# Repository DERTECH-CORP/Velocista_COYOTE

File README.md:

# Velocista "Coyote" - Robot Seguidor de Línea

## Descripción

El velocista "Coyote" es un robot seguidor de línea de alto rendimiento diseñado para competir en desafíos de velocidad y precisión. Este repositorio contiene el firmware, el diseño de hardware electrónico y los modelos 3D relacionados con el robot Coyote. Aquí encontrarás toda la información necesaria para comprender el robot seguidor de línea Coyote.

## Características principales

- **Seguimiento de línea preciso**: Coyote utiliza los sensores ópticos QRE1113 para seguir líneas con precisión y rapidez. Su firmware incorpora algoritmos de control PID que garantizan un seguimiento suave y estable.

- **Velocidad y agilidad**: Utiliza sus motores de RPM2000 con diseño aerodinámico, El Coyote puede alcanzar altas velocidades y realizar maniobras bruscas gracias a sus ruedas anchas que le ayudan a tener mejor agarre en la pista.

- **Firmware personalizable**: El firmware del robot está escrito en lenguaje C++ y se basa en la plataforma de desarrollo ESP32. Este micricontrolador nos ayuda mucho ya que tiene antena wifi/bluetooth integrada y gracias a eso podemos debuguear y calibrar el robot sin necesidad de conectarlo a la computadora.

## Contenido del repositorio

- **/firmware**: En esta carpeta encontrarás el código fuente del firmware utilizado en Coyote. El firmware está escrito en lenguaje C++ y se basa en la plataforma de desarrollo ESP32. Incluye los algoritmos de control, la lógica de seguimiento de línea y la comunicación con los sensores y actuadores del robot ademas de la interfaz bluetooth.

- **/hardware**: Aquí se encuentran los diseños y esquemas del hardware electrónico utilizado en Coyote. Estos archivos incluyen los esquemas de conexión y los diagramas de circuitos.

- **/3D**: En esta carpeta encontrarás los modelos 3D del robot Coyote. Se pueden utilizar para visualizar, modificar y fabricar las partes físicas del robot.

¡Gracias por tu interés en Coyote!

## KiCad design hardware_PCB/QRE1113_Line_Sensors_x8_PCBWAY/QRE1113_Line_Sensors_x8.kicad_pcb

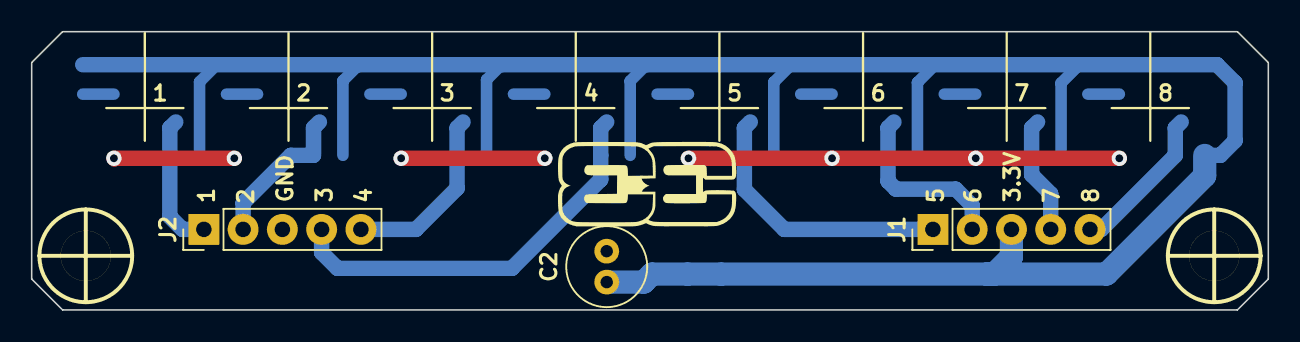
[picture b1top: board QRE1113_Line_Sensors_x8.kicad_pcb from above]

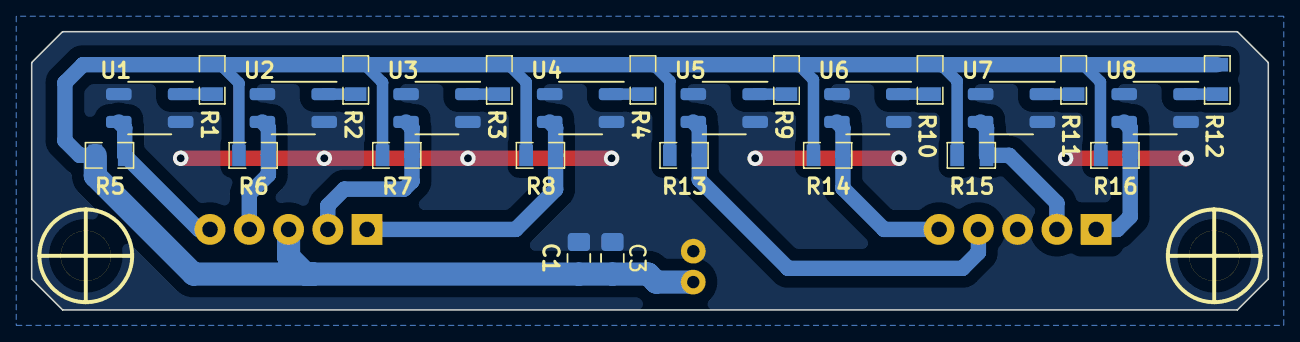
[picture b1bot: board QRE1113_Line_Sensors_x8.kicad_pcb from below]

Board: 2 copper layers, 80.0 x 18.0 mm, 31 parts (26 on the bottom side), 18 nets.

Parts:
C1, C3: 100nf; C_0805_2012Metric_Pad1.18x1.45mm_HandSolder
C2: 100uf; C_Radial_D5.0mm_H11.0mm_P2.00mm
H1, H2: HOLE; Separador_M3_5mm
J1, J2: Conn_01x05_Pin; PinHeader_1x05_P2.54mm_Vertical
R1, R2, R3, R4, R9, R10, R11, R12: 100; R_0805
R5, R6, R7, R8, R13, R14, R15, R16: 10k; R_0805
U1, U2, U3, U4, U5, U6, U7, U8: QRE1113GR; OnSemi_CASE100CY

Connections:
+3V3: C1.1, C2.1, C3.1, J1.3, R1.1, R2.1, R3.1, R4.1, R5.2, R6.2, R7.2, R8.2, R9.1, R10.1, R11.1, R12.1, R13.2, R14.2, R15.2, R16.2
/OUT_1: J1.5, R5.1, U1.3
/OUT_2: J1.4, R6.1, U2.3
/OUT_3: J1.2, R7.1, U3.3
/OUT_4: J1.1, R8.1, U4.3
/OUT_5: J2.4, R13.1, U5.3
/OUT_6: J2.5, R14.1, U6.3
/OUT_7: J2.2, R15.1, U7.3
/OUT_8: J2.1, R16.1, U8.3
GND: C1.2, C2.2, C3.2, J2.3, U1.2 (K), U1.4, U2.2 (K), U2.4, U3.2 (K), U3.4, U4.2 (K), U4.4, U5.2 (K), U5.4, U6.2 (K), U6.4, U7.2 (K), U7.4, U8.2 (K), U8.4
unnamed: R1.2, U1.1 (A)
unnamed: R2.2, U2.1 (A)
unnamed: R3.2, U3.1 (A)
unnamed: R4.2, U4.1 (A)
unnamed: R9.2, U5.1 (A)
unnamed: R10.2, U6.1 (A)
unnamed: R11.2, U7.1 (A)
unnamed: R12.2, U8.1 (A)

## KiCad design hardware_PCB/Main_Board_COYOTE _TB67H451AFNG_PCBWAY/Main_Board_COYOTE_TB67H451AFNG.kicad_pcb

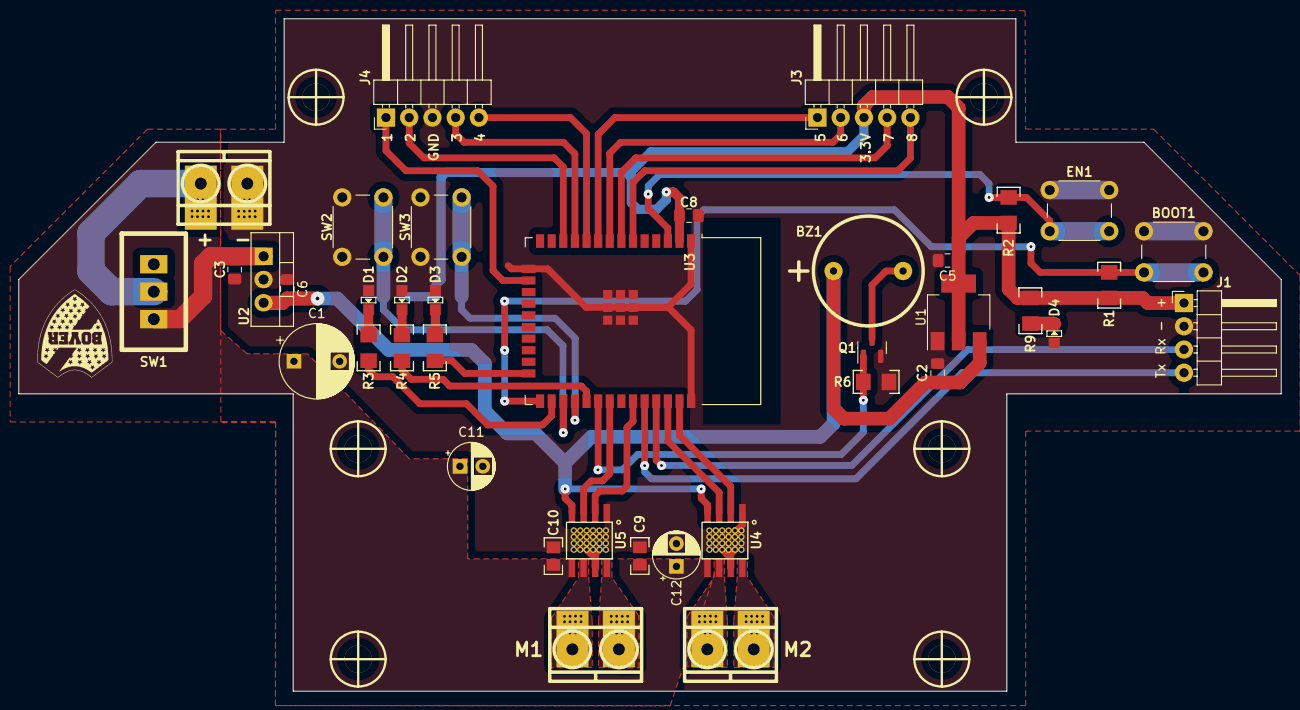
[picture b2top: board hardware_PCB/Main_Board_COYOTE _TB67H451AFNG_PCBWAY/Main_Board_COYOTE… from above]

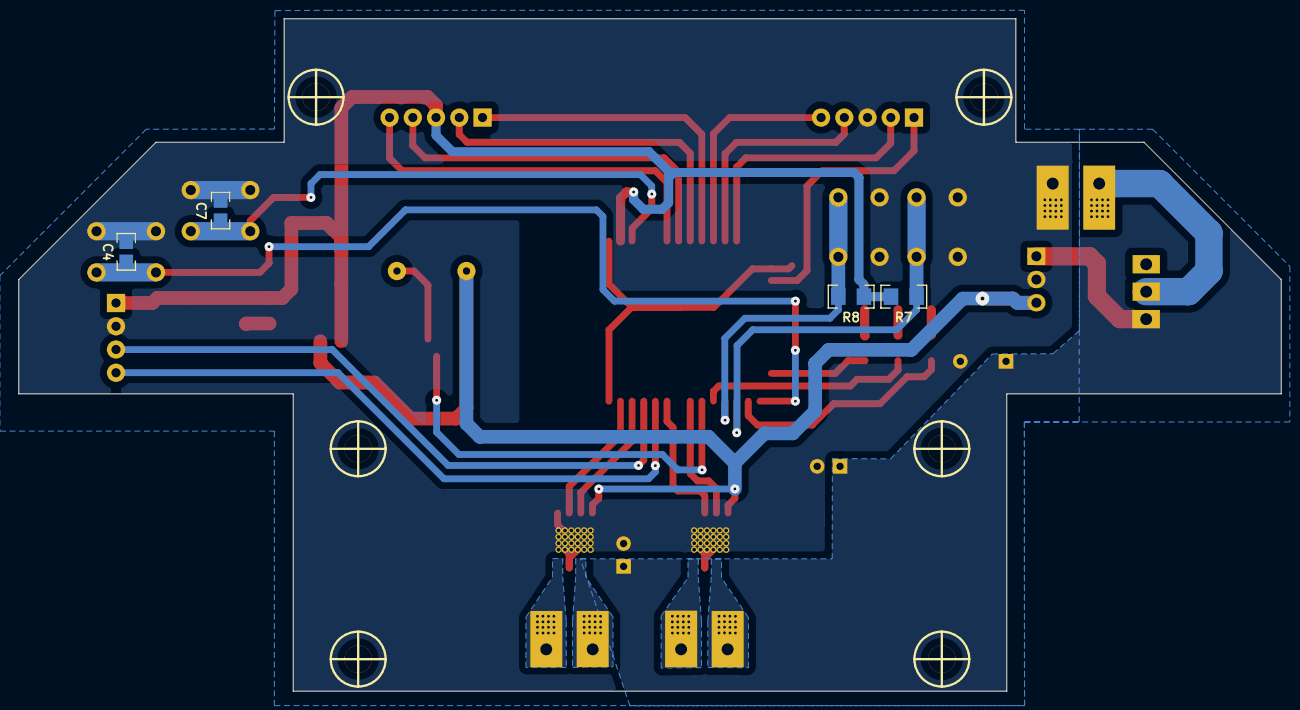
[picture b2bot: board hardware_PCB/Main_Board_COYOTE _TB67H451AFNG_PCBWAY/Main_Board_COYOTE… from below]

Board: 2 copper layers, 138.0 x 73.5 mm, 49 parts (4 on the bottom side), 36 nets.

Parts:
BOOT1: SW_Push; SW_PUSH_6mm_H5mm
BZ1: Buzzer; Buzzer_12mm
C1: 100uF 35V; CP_Radial_D8.0mm_P5.00mm
C2, C3, C5, C6, C8: 1uF; C_0805_2012Metric_Pad1.18x1.45mm_HandSolder
C4, C7: 1n; C_0805
C9, C10: 100nF; C_0805
C11, C12: 100uF 35V; CP_Radial_D5.0mm_P2.50mm
D1, D2, D3, D4: LED; Led_0805
EN1: SW_Push; SW_PUSH_6mm_H5mm
H1, H2, H3, H4, H5, H6: Mounting_Hole; hole_3mm
J1: FTDI; PinHeader_1x04_P2.54mm_Horizontal
J2: + -; BORNERA2_AZUL_VIAS
J3, J4: Conn_01x05_Pin; PinHeader_1x05_P2.54mm_Horizontal
J5: M2; BORNERA2_AZUL_VIAS
J6: M1; BORNERA2_AZUL_VIAS
Q1: 2N7002; SOT-23
R1: 1OK; R_1206
R2, R6: 10K; R_1206
R3, R4, R5, R9: 220; R_1206
R7, R8: 4K7; R_1206
SW1: SW_SPST; SW_SPDT_TH_Vertical
SW2: STRATEGY; SW_PUSH_6mm_H5mm
SW3: START; SW_PUSH_6mm_H5mm
U1: AMS1117-3.3; SOT-223-3_TabPin2
U2: LM7805_TO220; TO-220-3_Vertical
U3: ESP32-WROOM-32; ESP32-WROOM-32D
U4, U5: TB67H451AFNG; SSOP-8_disipa

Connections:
+3V3: C5.1, C8.2, J1.1, J3.3, R1.2, R2.2, R7.1, R8.1, R9.1, U1.2 (VO), U3.2 (VDD)
+5V: BZ1.1 (-), C2.1, C6.1, U1.3 (VI), U2.3 (VO), U4.4 (VREF), U5.4 (VREF)
/BOOT: BOOT1.2, C4.2, R1.1, U3.25 (IO0)
/BUZZER: Q1.1 (G), R6.1, U3.30 (IO18)
/EN: C7.2, EN1.2, R2.1, U3.3 (EN)
/LED_1: R4.1, U3.29 (IO5)
/LED_2: R3.1, U3.26 (IO4)
/LED_BUILTING: R5.1, U3.24 (IO2)
/M1A: U3.31 (IO19), U5.3 (IN1)
/M1B: U3.33 (IO21), U5.2 (IN2)
/M2A: U3.36 (IO22), U4.3 (IN1)
/M2B: U3.37 (IO23), U4.2 (IN2)
/OUT_1: J3.5, U3.6 (IO34)
/OUT_2: J3.4, U3.7 (IO35)
/OUT_3: J3.2, U3.8 (IO32)
/OUT_4: J3.1, U3.9 (IO33)
/OUT_5: J4.5, U3.10 (IO25)
/OUT_6: J4.4, U3.11 (IO26)
/OUT_7: J4.2, U3.12 (IO27)
/OUT_8: J4.1, U3.16 (IO13)
/PUSH_1: R7.2, SW2.2, U3.27 (IO16)
/PUSH_2: R8.2, SW3.2, U3.28 (IO17)
/Rx: J1.3, U3.35 (TXD0/IO1)
/Tx: J1.4, U3.34 (RXD0/IO3)
/VIN: J2.2, SW1.1 (A)
GND: BOOT1.1, C1.2, C2.2, C3.2, C4.1, C5.2, C6.2, C7.1, C8.1, C9.2, C10.2, C11.2, C12.2, D1.1 (K), D2.1 (K), D3.1 (K), D4.1 (K), EN1.1, J1.2, J2.1, J4.3, Q1.2 (S), R6.2, SW2.1, SW3.1, U1.1 (GND), U2.2 (GND), U3.1 (GND), U3.15 (GND), U3.38 (GND), U3.39 (GND), U4.1 (GND), U4.7 (RS), U5.1 (GND), U5.7 (RS)
unnamed: BZ1.2 (+), Q1.3 (D)
unnamed: D1.2 (A), R3.2
unnamed: D2.2 (A), R4.2
unnamed: D3.2 (A), R5.2
unnamed: D4.2 (A), R9.2
unnamed: J5.1, U4.6 (OUT1)
unnamed: J5.2, U4.8 (OUT2)
unnamed: J6.1, U5.6 (OUT1)
unnamed: J6.2, U5.8 (OUT2)
VCC: C1.1, C3.1, C9.1, C10.1, C11.1, C12.1, SW1.2 (B), U2.1 (VI), U4.5 (VM), U5.5 (VM)

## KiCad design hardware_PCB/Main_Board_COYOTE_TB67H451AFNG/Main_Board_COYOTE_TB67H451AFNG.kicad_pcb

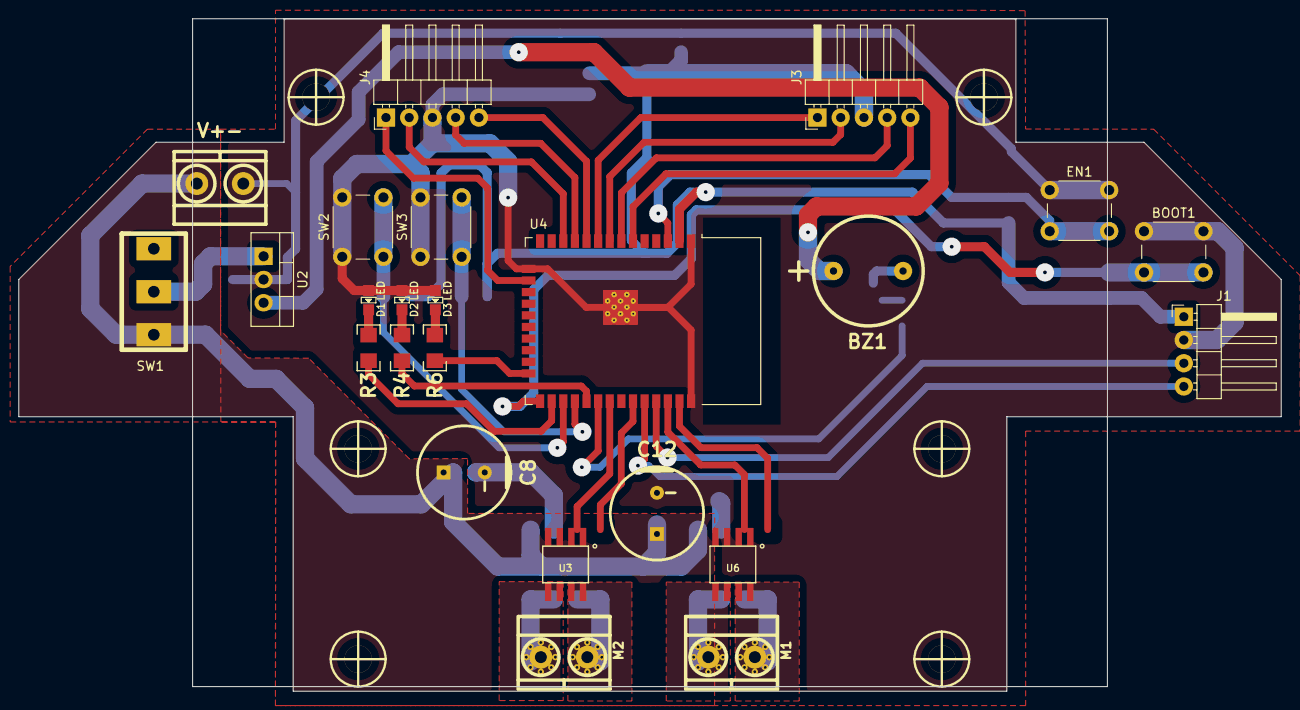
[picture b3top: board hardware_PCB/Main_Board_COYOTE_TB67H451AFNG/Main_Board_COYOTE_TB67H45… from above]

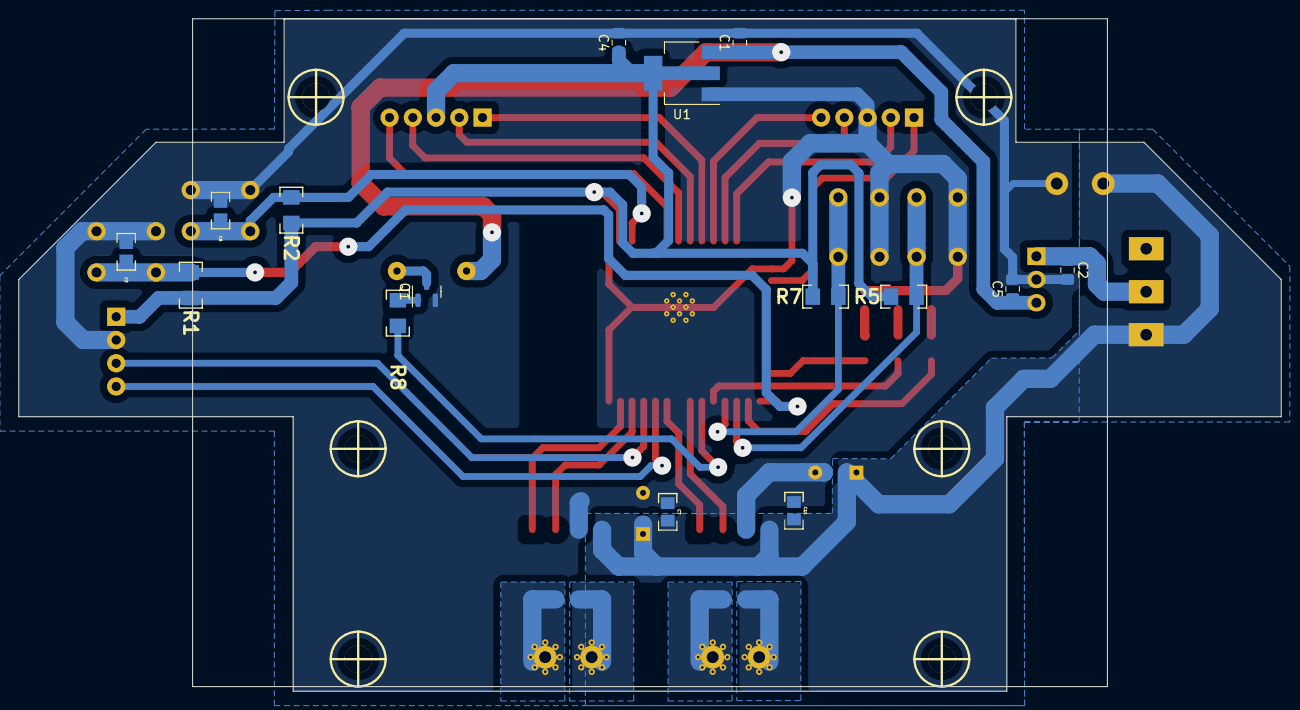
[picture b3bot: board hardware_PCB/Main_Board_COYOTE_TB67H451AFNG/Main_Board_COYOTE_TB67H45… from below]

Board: 2 copper layers, 138.0 x 73.5 mm, 45 parts (15 on the bottom side), 37 nets.

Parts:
BOOT1: SW_Push; SW_PUSH_6mm_H5mm
BZ1: Buzzer; Buzzer_12mm
C1, C2, C4, C5: 1uF; C_0805_2012Metric_Pad1.18x1.45mm_HandSolder
C3, C6: 1n; C_0805
C7, C11: 100nF; C_0805
C8, C12: 100uF 35V; CAP_ELEC_10X8mm
D1, D2, D3: LED; Led_0805
EN1: SW_Push; SW_PUSH_6mm_H5mm
H1, H2, H3, H4, H5, H6: Mounting_Hole; hole_3mm
J1: FTDI; PinHeader_1x04_P2.54mm_Horizontal
J2: V+-; BORNERA2_AZUL
J3, J4: Conn_01x05_Pin; PinHeader_1x05_P2.54mm_Horizontal
J9: M1; BORNERA2_AZUL_HOLES+
J10: M2; BORNERA2_AZUL_HOLES+
Q1: 2N7002; SOT-23
R1: 1OK; R_1206
R2, R8: 10K; R_1206
R3, R4, R6: 220; R_1206
R5, R7: 4K7; R_1206
SW1: SW_SPST; SW_SPDT_TH_Vertical
SW2, SW3: START; SW_PUSH_6mm_H5mm
U1: AMS1117-3.3; SOT-223-3_TabPin2
U2: LM7805_TO220; TO-220-3_Vertical
U3, U6: TB67H451AFNG; SSOP-8
U4: ESP32-WROOM-32; ESP32-WROOM-32D

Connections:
+3V3: C4.1, J1.1, J3.3, R1.2, R2.2, R5.1, R7.1, U1.2 (VO), U4.2 (VDD)
+5V: BZ1.1 (-), C1.1, C5.1, U1.3 (VI), U2.3 (VO), U3.4 (VREF), U6.4 (VREF)
/BOOT: BOOT1.2, C3.2, R1.1, U4.25 (IO0)
/BUZZER: R8.2, U4.30 (IO18)
/EN: C6.2, EN1.2, R2.1, U4.3 (EN)
/LED_1: R4.1, U4.29 (IO5)
/LED_2: R3.1, U4.26 (IO4)
/LED_BUILTING: R6.1, U4.24 (IO2)
/M1A: U4.31 (IO19), U6.2 (IN2)
/M1B: U4.33 (IO21), U6.3 (IN1)
/M2A: U3.2 (IN2), U4.36 (IO22)
/M2B: U3.3 (IN1), U4.37 (IO23)
/OUT_1: J3.5, U4.6 (IO34)
/OUT_2: J3.4, U4.7 (IO35)
/OUT_3: J3.2, U4.8 (IO32)
/OUT_4: J3.1, U4.9 (IO33)
/OUT_5: J4.5, U4.10 (IO25)
/OUT_6: J4.4, U4.11 (IO26)
/OUT_7: J4.2, U4.12 (IO27)
/OUT_8: J4.1, U4.16 (IO13)
/PUSH_1: R5.2, SW2.2, U4.27 (IO16)
/PUSH_2: R7.2, SW3.2, U4.28 (IO17)
/Rx: J1.3, U4.35 (TXD0/IO1)
/Tx: J1.4, U4.34 (RXD0/IO3)
/Vin: C7.1, C8.1, C11.1, C12.1, U3.5 (VM), U6.5 (VM)
GND: BOOT1.1, C1.2, C2.2, C3.1, C4.2, C5.2, C6.1, C7.2, C8.2, C11.2, C12.2, D1.1 (K), D2.1 (K), D3.1 (K), EN1.1, J1.2, J2.1, J4.3, Q1.2 (S), SW2.1, SW3.1, U1.1 (GND), U2.2 (GND), U3.1 (GND), U3.7 (RS), U4.1 (GND), U4.15 (GND), U4.38 (GND), U4.39 (GND), U6.1 (GND), U6.7 (RS)
unnamed: BZ1.2 (+), Q1.3 (D)
unnamed: D1.2 (A), R3.2
unnamed: D2.2 (A), R4.2
unnamed: D3.2 (A), R6.2
unnamed: Q1.1 (G), R8.1
unnamed: C2.1, SW1.2 (B), U2.1 (VI)
unnamed: J10.1, U3.6 (OUT1)
unnamed: J10.2, U3.8 (OUT2)
unnamed: J9.1, U6.6 (OUT1)
unnamed: J9.2, U6.8 (OUT2)
VCC: J2.2, SW1.1 (A)

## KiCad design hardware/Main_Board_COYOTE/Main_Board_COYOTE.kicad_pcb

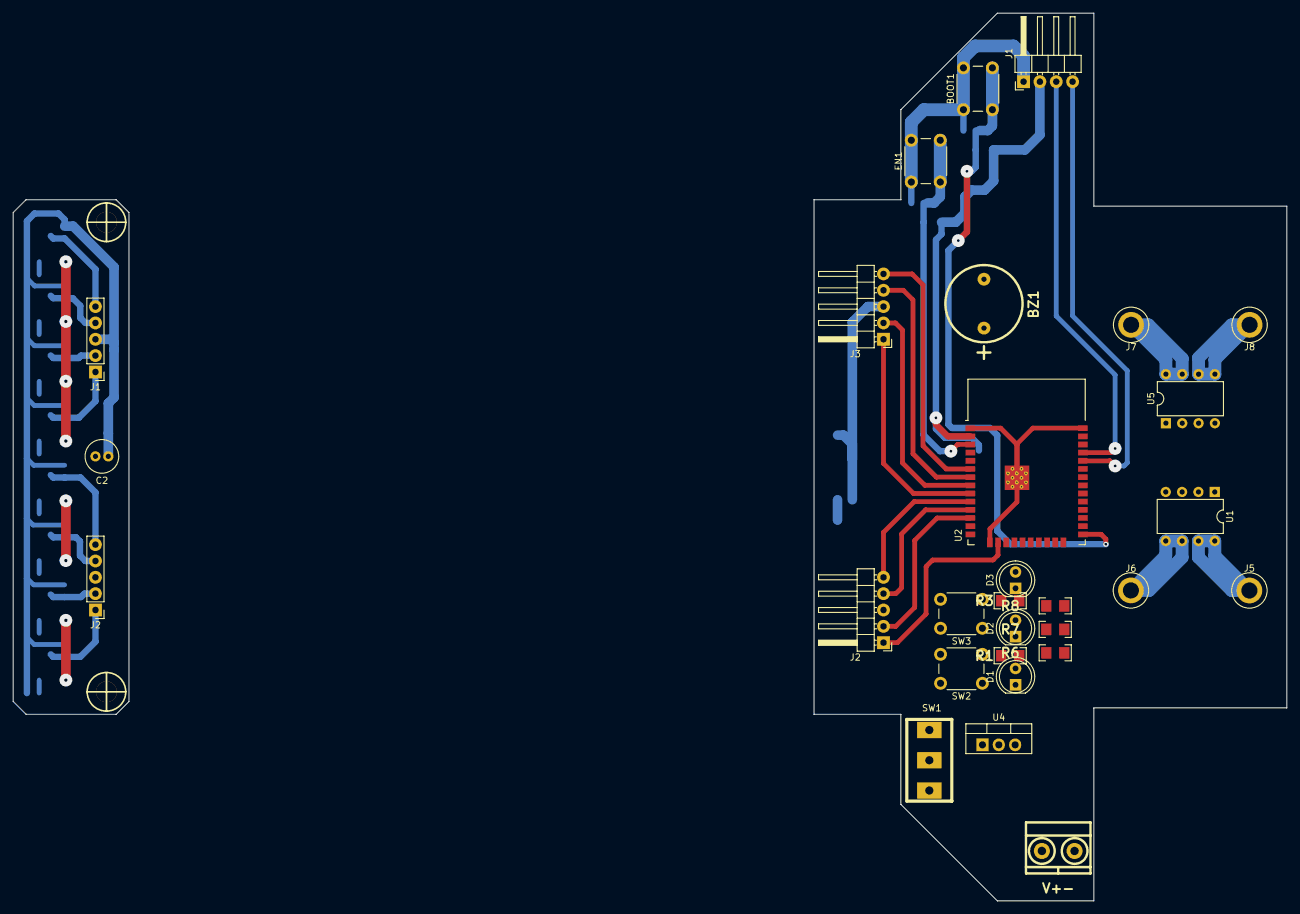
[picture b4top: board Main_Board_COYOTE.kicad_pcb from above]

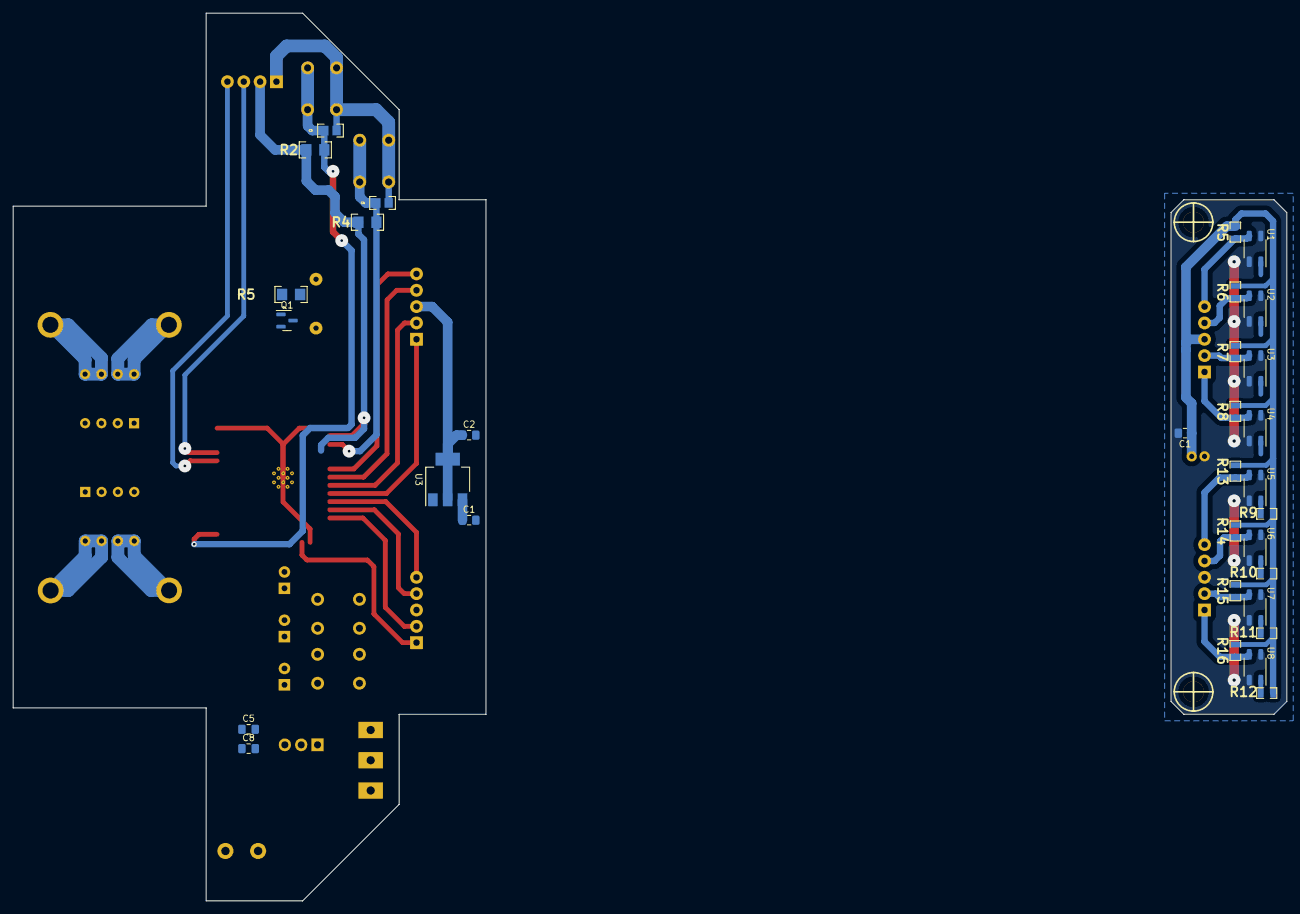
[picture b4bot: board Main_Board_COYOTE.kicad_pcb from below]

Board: 2 copper layers, 198.0 x 138.0 mm, 63 parts (32 on the bottom side), 37 nets.

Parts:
BOOT1: SW_Push; SW_PUSH_6mm_H5mm
BZ1: Buzzer; Buzzer_12mm
C1: 100nf; C_0805_2012Metric_Pad1.18x1.45mm_HandSolder
C1#2, C2#2, C5, C8: 1uF; C_0805_2012Metric_Pad1.18x1.45mm_HandSolder
C2: 100uf; C_Radial_D5.0mm_H11.0mm_P2.00mm
C3, C4: 1n; C_0805
D1, D2, D3: LED; LED_D5.0mm
EN1: SW_Push; SW_PUSH_6mm_H5mm
H1, H2: HOLE; Separador_M3_5mm
J1, J2: Conn_01x05_Pin; PinHeader_1x05_P2.54mm_Vertical
J1#2: FTDI; PinHeader_1x04_P2.54mm_Horizontal
J2#2, J3: Conn_01x05_Pin; PinHeader_1x05_P2.54mm_Horizontal
J4: V+-; BORNERA2_AZUL
J5, J7: MOTOR_PINM1A; Banana_Jack_1Pin
J6, J8: MOTOR_PINM1B; Banana_Jack_1Pin
Q1: 2N7002; SOT-23
R1, R3: 4K7; R_1206
R2: 1OK; R_1206
R4, R5: 10K; R_1206
R5#2, R6#2, R7#2, R8#2, R13, R14, R15, R16: 10k; R_0805
R6, R7, R8: 220; R_1206
R9, R10, R11, R12: 100; R_0805
SW1: SW_SPST; SW_SPDT_TH_Vertical
SW2, SW3: START; SW_PUSH_6mm_H5mm
U1, U5: TA6586; DIP-8_W7.62mm
U1#2, U2#2, U3#2, U4#2, U5#2, U6, U7, U8: QRE1113GR; OnSemi_CASE100CY
U2: ESP32-WROOM-32; ESP32-WROOM-32D
U3: AMS1117-3.3; SOT-223-3_TabPin2
U4: LM7805_TO220; TO-220-3_Vertical

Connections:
+3V3: C1.1, C2.1, C2#2.1, J1.3, J1#2.2, J3.3, R1.1, R2.2, R3.1, R4.2, R5#2.2, R6#2.2, R7#2.2, R8#2.2, R9.1, R10.1, R11.1, R12.1, R13.2, R14.2, R15.2, R16.2, U2.2 (VDD), U3.2 (VO)
+5V: BZ1.1 (-), C5.1, U4.3 (VO)
/BOOT: BOOT1.2, C3.2, R2.1, U2.25 (IO0)
/BUZZER: R5.2, U2.30 (IO18)
/EN: C4.2, EN1.2, R4.1, U2.3 (EN)
/LED_1: R6.1, U2.26 (IO4)
/LED_2: R7.1, U2.29 (IO5)
/LED_BUILTING: R8.1, U2.24 (IO2)
/M1A: U1.1 (IN1), U2.31 (IO19)
/M1B: U1.2 (IN2), U2.33 (IO21)
/M2A: U2.36 (IO22), U5.1 (IN1)
/M2B: U2.37 (IO23), U5.2 (IN2)
/OUTM1A: J5.1, U1.7 (OUT2), U1.8 (OUT2)
/OUTM1B: J6.1, U1.5 (OUT1), U1.6 (OUT1)
/OUTM2A: J7.1, U5.7 (OUT2), U5.8 (OUT2)
/OUTM2B: J8.1, U5.5 (OUT1), U5.6 (OUT1)
/OUT_1: J3.5, U2.6 (IO34)
/OUT_2: J3.4, U2.7 (IO35)
/OUT_3: J3.2, U2.8 (IO32)
/OUT_4: J3.1, U2.9 (IO33)
/OUT_5: J2#2.5, U2.10 (IO25)
/OUT_6: J2#2.4, U2.11 (IO26)
/OUT_7: J2#2.2, U2.12 (IO27)
/OUT_8: J2#2.1, U2.16 (IO13)
/PUSH_1: R1.2, SW2.2, U2.27 (IO16)
/PUSH_2: R3.2, SW3.2, U2.28 (IO17)
/Rx: J1#2.3, U2.35 (TXD0/IO1)
/Tx: J1#2.4, U2.34 (RXD0/IO3)
Earth: C5.2, C8.2, D1.1 (K), D2.1 (K), D3.1 (K), U4.2 (GND)
GND: BOOT1.1, C1.2, C1#2.2, C2.2, C2#2.2, C3.1, C4.1, EN1.1, J1#2.1, J2.3, J2#2.3, J4.2, Q1.2 (S), SW2.1, SW3.1, U1.3 (GND), U1#2.2 (K), U1#2.4, U2.1 (GND), U2.15 (GND), U2.38 (GND), U2.39 (GND), U2#2.2 (K), U2#2.4, U3.1 (GND), U3#2.2 (K), U3#2.4, U4#2.2 (K), U4#2.4, U5.3 (GND), U5#2.2 (K), U5#2.4, U6.2 (K), U6.4, U7.2 (K), U7.4, U8.2 (K), U8.4
unnamed: BZ1.2 (+), Q1.3 (D)
unnamed: D1.2 (A), R6.2
unnamed: D2.2 (A), R7.2
unnamed: D3.2 (A), R8.2
unnamed: Q1.1 (G), R5.1
unnamed: C1#2.1, C8.1, SW1.2 (B), U3.3 (VI), U4.1 (VI)
VCC: J4.1, SW1.1 (A), U1.4 (VM), U5.4 (VM)

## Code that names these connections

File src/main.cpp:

#include "BluetoothSerial.h"
#include <QTRSensors.h>
#include <Motor.h>

#if !defined(CONFIG_BT_ENABLED) || !defined(CONFIG_BLUEDROID_ENABLED)
#error Bluetooth is not enabled! Please run `make menuconfig` to and enable it
#endif

// boleano para que se ejecute el pid
bool run = false;

#define M1A 19
#define M1B 21
#define M2A 23
#define M2B 22
#define M1A_CHANEL 12
#define M1B_CHANEL 14
#define M2A_CHANEL 13
#define M2B_CHANEL 15

#define BUTTON 16

// valores pre definidos

// para sumar o restar velocidades
#define VALUE_5 5

// para sumar o restar el gate
#define VALUE_500 500

// para sumar o restas a
//  kp, ki, kd
#define VALUE_0_1 0.1
#define VALUE_0_01 0.01

#define COMPENSATION_PWM 5

int proportional = 0;
int derivative = 0;
int integral = 0;
int lastErr = 0;

// variables configurables para el pid
float kp = 0.03;
float ki = 0;
float kd = 0.06;

float speed = 0;

// velocidad crucero es la velocidad que se
// utiliza para el pid y es el pico en rectas
int velocity = 90;

int velocityTurn = 120;

// floats para almacenar los valores de los pid
// de cada motor
float pidLeft = 0;
float pidRight = 0;

// estos son los valores maximos y minimos
// de los motores cuando se le aplica el pid
int maxSpeed = 150;
int minSpeed = 0;

// gete es la barrera que sirve como flag
// para las condicionales de giro
int gateLeft = 5000;
int gateRight = 6000;

// lock : es el pwm  que va a
// usar el motor para frenar
int lockLeft = 75;
int lockRight = 80;

BluetoothSerial SerialBT;

QTRSensors qtr;

MOTOR *motorLeft = new MOTOR(M1B, M1A, M1B_CHANEL, M1A_CHANEL);

MOTOR *motorRight = new MOTOR(M2A, M2B, M2B_CHANEL, M2A_CHANEL);

// setpoint : es el punto en el que se desea
int setpoint = 5500;

const uint8_t SensorCount = 8;
uint16_t sensorValues[SensorCount];

int Led = 5;
int LedB = 2;

void calibration()
{
  qtr.setTypeAnalog();
  qtr.setSensorPins((const uint8_t[]){
                        13, 27, 25, 26, 33, 32, 35, 34},
                    SensorCount);

  delay(500);
  pinMode(Led, OUTPUT);
  digitalWrite(Led, HIGH);
  for (uint16_t i = 0; i < 500; i++)
  {
    qtr.calibrate();
  }
  digitalWrite(Led, LOW);
}

// funcion que nos va a retornar la posicion
//  de la linea
int getPosition()
{
  int position = qtr.readLineWhite(sensorValues);
  return position;
}



void PID()
{
  int position = getPosition();

  proportional = position - setpoint;

  derivative = proportional - lastErr;

  integral += proportional;

  speed = (proportional * kp) + (derivative * kd) + (integral * ki);

  lastErr = proportional;

  pidLeft = (velocity + speed + COMPENSATION_PWM);
  pidRight = (velocity - speed);

  if (pidLeft > maxSpeed + COMPENSATION_PWM)
    pidLeft = maxSpeed + COMPENSATION_PWM;
  else if (pidLeft < minSpeed)
    pidLeft = minSpeed;

  if (pidRight < minSpeed)
    pidRight = minSpeed;
  else if (pidRight > maxSpeed)
    pidRight = maxSpeed;

  if (position >= gateRight)
  {

    motorLeft->GoAvance(velocityTurn);
    motorRight->GoBack(lockRight);

    
  }
  else if (position <= gateLeft)
  {

    motorLeft->GoBack(lockLeft);
    motorRight->GoAvance(velocityTurn);

    
  }
  else
  {
    motorLeft->GoAvance(pidLeft);
    motorRight->GoAvance(pidRight);
  }
}

// funcion que imprime un menu por bluetooth
void printOptions()
{
  // clean the serial
  for (int i = 0; i < 10; i++)
  {
    SerialBT.println("");
  }

  SerialBT.println("Configuracion Actual:");

  SerialBT.print("- KP = ");
  SerialBT.println(kp);

  SerialBT.print("- KI = ");
  SerialBT.println(ki);

  SerialBT.print("- KD = ");
  SerialBT.println(kd);

  SerialBT.print("- maxSpeed = ");
  SerialBT.println(maxSpeed);

  SerialBT.print("- lockLeft = ");
  SerialBT.println(lockLeft);

  SerialBT.print("- lockRight = ");
  SerialBT.println(lockRight);

  SerialBT.print("- gateLeft = ");
  SerialBT.println(gateLeft);

  SerialBT.print("- gateRight = ");
  SerialBT.println(gateRight);

  SerialBT.print("- velocityTurn = ");
  SerialBT.println(velocityTurn);

  SerialBT.println(" (K) KP + 0.1 / (L) KP - 0.1");
  SerialBT.println(" (Q) KP + 0.01 / (W) KP - 0.01");

  SerialBT.println(" (R) KI + 0.1 / (T) KI - 0.1");
  SerialBT.println(" (U) KI + 0.01 / (I) KI - 00.1");

  SerialBT.println(" (Z) KD + 0.1 / (X) KD - 0.1");
  SerialBT.println(" (G) KD + 0.01 / (H) KD - 00.1");

  SerialBT.println(" (1) lockLeft + 5 / (2) lockLeft - 5");
  SerialBT.println(" (3) lockRight + 5 / (4) lockRight - 5");

  SerialBT.println(" (5) maxSpeed + 5 / (6) maxSpeed - 5");

  SerialBT.println(" (7) gateLeft + 500 / (8) gateLeft - 500");
  SerialBT.println(" (9) gateRight + 500 / (0) gateRight - 500");

  SerialBT.println(" (+) velocityTurn + 1 / (-) velocityTurn - 1");

  SerialBT.println(" (F) para ver la posicion");
}

void menuBT()
{
  if (SerialBT.available())
  {
    char Menssage = SerialBT.read();
    switch (Menssage)
    {
    case 'M':
    {
      printOptions();
      break;
    }
    case 'A':
    {
      run = true;
      break;
    }
    case 'B':
    {
      run = false;
      break;
    }
    case 'K':
    {
      kp += VALUE_0_1;
      printOptions();
      break;
    }
    case 'L':
    {
      kp -= VALUE_0_1;
      printOptions();
      break;
    }
    case 'Q':
    {
      kp += VALUE_0_01;
      printOptions();
      break;
    }
    case 'W':
    {
      kp -= VALUE_0_01;
      printOptions();
      break;
    }

    case 'R':
    {
      ki += VALUE_0_1;
      printOptions();
      break;
    }
    case 'T':
    {
      ki -= VALUE_0_1;
      printOptions();
      break;
    }
    case 'U':
    {
      ki += VALUE_0_01;
      printOptions();
      break;
    }
    case 'I':
    {
      ki -= VALUE_0_01;
      printOptions();
      break;
    }

    case 'Z':
    {
      kd += VALUE_0_1;
      printOptions();
      break;
    }
    case 'X':
    {
      kd -= VALUE_0_1;
      printOptions();
      break;
    }
    case 'G':
    {
      kd += VALUE_0_01;
      printOptions();
      break;
    }
    case 'H':
    {
      kd -= VALUE_0_01;
      printOptions();
      break;
    }
    case 'F':
    {
      SerialBT.println(getPosition());
      break;
    }
    case '1':
    {
      lockLeft += VALUE_5;
      printOptions();
      break;
    }
    case '2':
    {
      lockLeft -= VALUE_5;
      printOptions();
      break;
    }
    case '3':
    {
      lockRight += VALUE_5;
      printOptions();
      break;
    }
    case '4':
    {
      lockRight -= VALUE_5;
      printOptions();
      break;
    }
    case '5':
    {
      maxSpeed += VALUE_5;
      printOptions();
      break;
    }
    case '6':
    {
      maxSpeed -= VALUE_5;
      printOptions();
      break;
    }
    case '7':
    {
      gateLeft += VALUE_500;
      printOptions();
      break;
    }
    case '8':
    {
      gateLeft -= VALUE_500;
      printOptions();
      break;
    }
    case '9':
    {
      gateRight += VALUE_500;
      printOptions();
      break;
    }
    case '0':
    {
      gateRight -= VALUE_500;
      printOptions();
      break;
    }
    case '+':
    {
      velocityTurn += 1;
      printOptions();
      break;
    }
    case '-':
    {
      velocityTurn -= 1;
      printOptions();
      break;
    }

    default:
      break;
    }
  }
}

void setup()
{
  SerialBT.begin("coyote");
  pinMode(Led, OUTPUT);
  calibration();
  pinMode(LedB, OUTPUT);
  pinMode(BUTTON, INPUT);
  digitalWrite(LedB, HIGH);
}

bool isPress = false;

void loop()
{
  if (digitalRead(BUTTON) == LOW) isPress = true;

  menuBT();

SerialBT.println(getPosition());

  if (isPress)
  {
    PID();
  }
}

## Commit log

2023-06-11 Creacion de la carpeta hardware
2023-07-30 Creacion del PCB de sensores QRE1113, y desarrollo del mismo
2023-08-02 Creacion del SCH de la main board
2023-08-02 Creacion croquis Velocista
2023-08-04 Creacion finalizacion del croquis velocista
2023-08-04 Edicion SCh y PCB de la main board
2023-08-05 SCH del velocista terminado
2023-08-06 Ultimas mejoras del PCB main e inicio del modelo 3D
2023-08-06 Terminados los PCBs
2023-08-07 Se diseño el modelo 3D de la rueda
2023-08-17 Creacion del soporte de varillas
2023-08-17 Se crearon los modelos 3D de los sportes de placas, varillas y motores
2023-09-04 Agegrado PINOUT placa coyote
2023-09-08 add lib qtr
2023-09-08 Add library Motor version Esp
2023-09-13 Test bluetooth
2023-09-14 define sensors
2023-09-14 calibration and getPosition
2023-09-14 Fix error sensors
2023-09-15 P.I.D
2023-09-22 Code legacy
2023-09-22 update lib MOTOR
2023-09-22 Test with bluetooth and motors
2023-09-22 panel with bluetooth
2023-09-24 case menu PID
2023-10-03 PID v6
2023-10-05 refactor
2023-10-06 update map
2023-10-06 Button
2023-10-06 Frenos
2023-10-07 anda
2023-10-09 se sale en las curvas
2023-10-11 folder
2023-10-11 Pull request software-development with main
2023-10-12 Update_v2 README.md
2023-10-15 new folder
2023-10-15 test
2023-10-16 update pid
2023-10-25 test 2s 200
2023-10-26 eu confio
2023-10-26 frenos test
2023-10-26 se redujo calibracion
2023-10-26 version que anda
2023-10-26 Anda a 200
2023-10-27 anda a 220
2023-10-27 velocidad a 250
2023-10-27 ultimo de lo ultimo
2023-10-28 2s 255 pasa
2023-10-28 3s 190
2023-10-28 aaaa
2023-10-31 Agregue los PCB para fabricar
2023-11-08 2s 255
2023-11-09 test de la tarde
2023-11-10 chore: add logs class
2023-11-11 misiones
2023-11-11 3s 180
2023-11-13 240 3s
